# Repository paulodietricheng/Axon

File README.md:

# Axon

Axon is a single-channel mixed-signal Electromyography (EMG) acquisition and actuation system built around a custom PCB. It combines a low-noise analog front end, delta-sigma analog-to-digital conversion, and STM32 firmware for real-time signal acquisition and control of external devices.

The project emphasizes signal integrity, deterministic signal paths, and hardware/firmware co-design in a timing-constrained embedded system.

## System Architecture
Axon implements a linear signal-processing pipeline from electrodes to digital processing:

- Electrodes  
- Input Protection  
- Instrumentation Amplifier  
- Active Band-Pass Filtering  
- Delta-Sigma ADC  
- STM32 (SPI)  
- Actuation Outputs

## Analog Front End

### Input Protection
- 100 kΩ series resistor at the electrode input
- Schottky diode clamps to +5 V and −5 V
- Protects downstream circuitry from transients and overvoltage events

### Instrumentation Amplifier
- INA333 instrumentation amplifier
- Gain: 20×
- Chosen for high CMRR (~100 dB) to suppress common-mode noise inherent in EMG signals
- Reference voltage provided by a buffered ground generated using an OPA333

### Active Filtering
All active filters use OPA333 op-amps for low offset and low noise.

- High-pass Sallen–Key filter  
  - Cutoff frequency: 15 Hz  
  - Linear gain  
  - Removes DC offset and motion artifacts

- Low-pass Sallen–Key filter  
  - Cutoff frequency: 450 Hz
  - Gain: 5×
  - Limits high-frequency noise and out-of-band content

## Analog-to-Digital Conversion

- ADS131M02 delta-sigma ADC
- Differential inputs:
  - Filtered signal routed through 1 kΩ resistors to AIN0P and AIN1P
  - AIN0N and AIN1N tied to buffered ground
- ADC clock provided by an ASE 8.192 MHz oscillator
- Design considers conversion latency and group delay inherent to delta-sigma architectures

## Digital Processing & Control

### Microcontroller
- STM32 microcontroller
- Communicates with ADC via SPI
- Handles data acquisition, processing, and output control

### Programming & Debug
- JTAG / SWD interface exposed
- Signals:
  - SWDIO, SWCLK, SWO, RESET
  - RXI, TXO
  - VREF = 3.3 V

### Outputs
- Three MCU-controlled output pins routed to an external connector
- Intended for actuation or control of external devices

## Power Architecture

- USB-C power input
- Protection fuse on input
- Power rails:
  - +5 V from USB
  - −5 V generated via TPS7A inverter
  - 3.3 V generated via TPS604 DC-DC converter

## PCB Layout

- 4-layer PCB stackup:
  1. Signal
  2. Ground plane
  3. Power pours
  4. Signal
- Layout prioritizes:
  - Low-noise analog routing
  - Solid ground reference
  - Separation of analog and digital domains

## Notes

Axon serves as a completed mixed-signal system demonstrating practical considerations in low-level analog design, real-time embedded firmware, and end-to-end signal path analysis.

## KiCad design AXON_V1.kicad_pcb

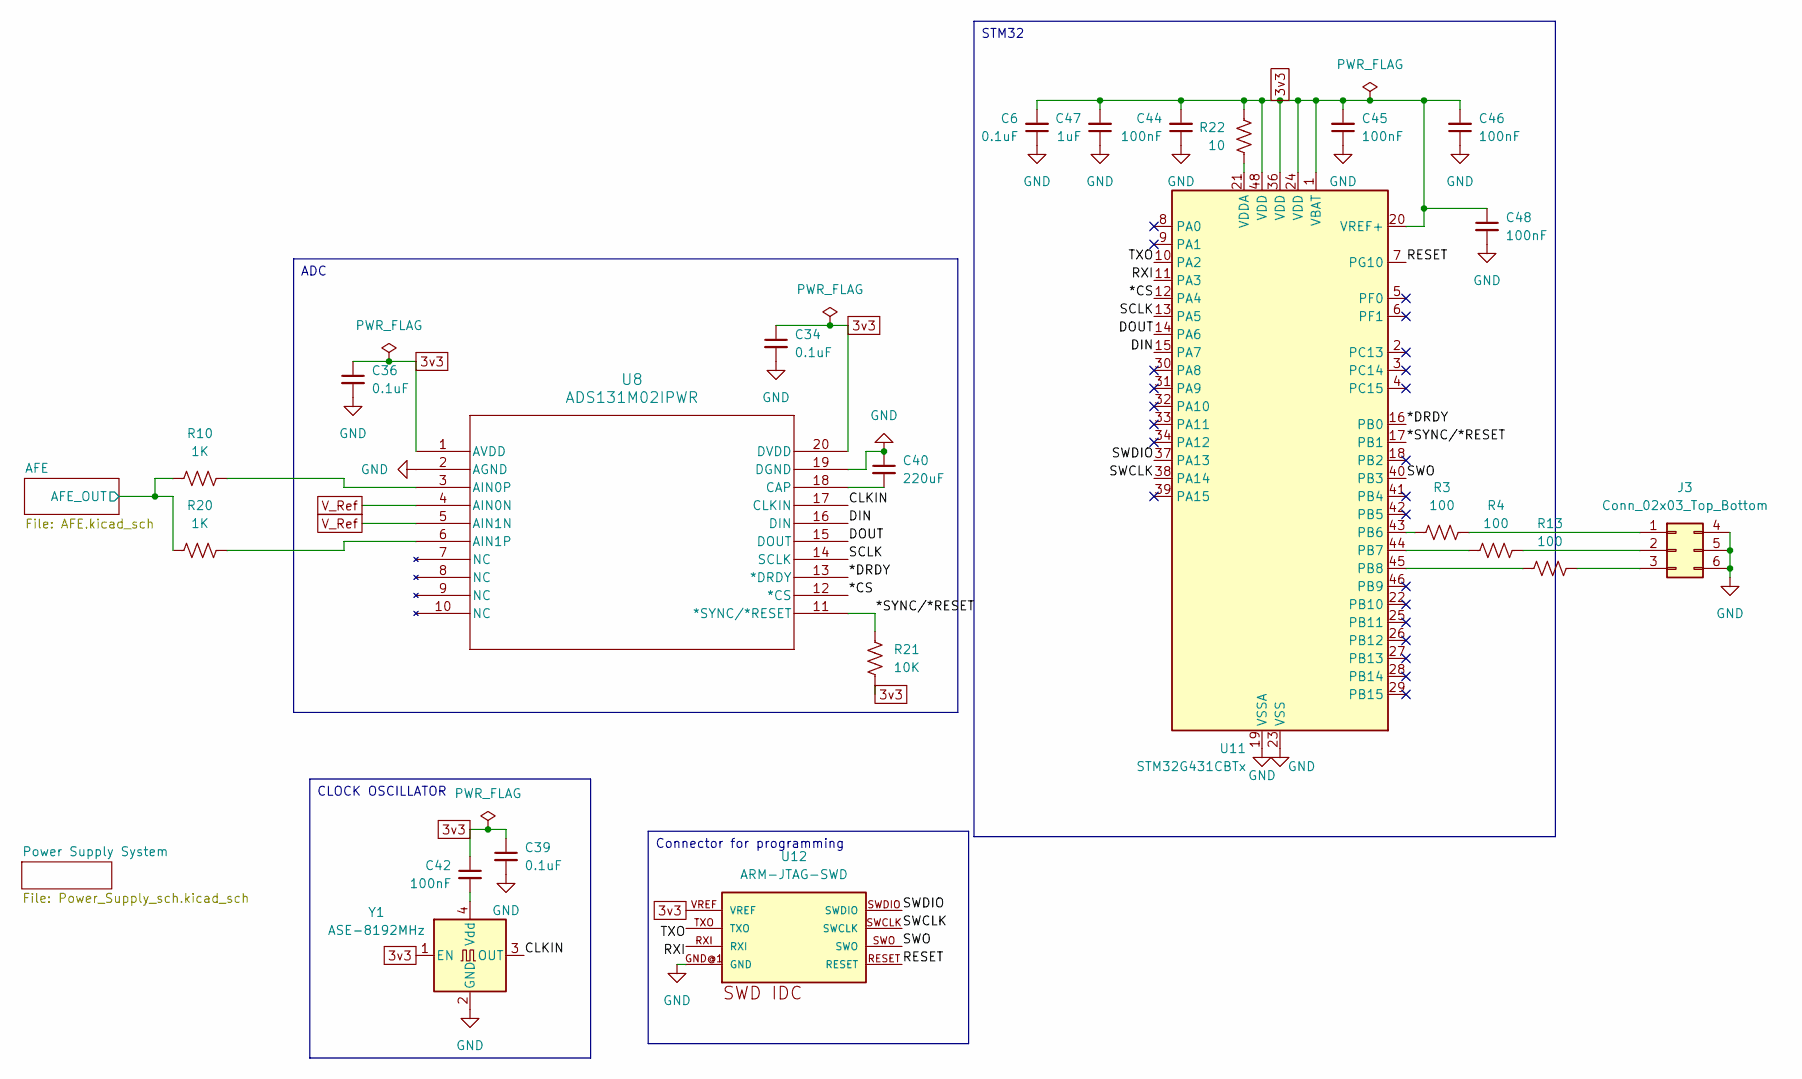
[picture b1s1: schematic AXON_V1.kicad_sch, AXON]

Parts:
C6, C34, C36, C39: 0.1uF; C_0201_0603Metric
C40: 220uF; C_0201_0603Metric
C42, C44, C45, C46, C48: 100nF; C_0201_0603Metric
C47: 1uF; C_0201_0603Metric
J3: Conn_02x03_Top_Bottom; PinSocket_2x03_P2.54mm_Vertical
R3, R4, R13: 100; R_0201_0603Metric
R10, R20: 1K; R_0201_0603Metric
R21: 10K; R_0201_0603Metric
R22: 10; R_0201_0603Metric
U8: ADS131M02IPWR; TSSOP20_PW_TEX
U11: STM32G431CBTx; LQFP-48_7x7mm_P0.5mm
U12: ARM-JTAG-SWD; ARM-JTAG-10-SWD-IDC
Y1: ASE-8192MHz; Oscillator_SMD_Abracon_ASE-4Pin_3.2x2.5mm

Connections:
3v3: C6.2, C34.1, C36.1, C39.1, C42.1, C44.2, C45.2, C46.2, C47.2, C48.1, R21.2, R22.1, U8.1 (AVDD), U8.20 (DVDD), U11.1 (VBAT), U11.20 (VREF+), U11.24 (VDD), U11.36 (VDD), U11.48 (VDD), U12.VREF, Y1.1 (EN); also elsewhere on the board
/*CS: U8.12 (*CS), U11.12 (PA4)
/*DRDY: U8.13 (*DRDY), U11.16 (PB0)
/*SYNC/*RESET: R21.1, U8.11 (*SYNC/*RESET), U11.17 (PB1)
/AFE/AFE_OUT: R10.1, R20.1; also elsewhere on the board
/CLKIN: U8.17 (CLKIN), Y1.3 (OUT)
/DIN: U8.16 (DIN), U11.15 (PA7)
/DOUT: U8.15 (DOUT), U11.14 (PA6)
/RESET: U11.7 (PG10), U12.RESET
/RXI: U11.11 (PA3), U12.RXI
/SCLK: U8.14 (SCLK), U11.13 (PA5)
/SWCLK: U11.38 (PA14), U12.SWCLK
/SWDIO: U11.37 (PA13), U12.SWDIO
/SWO: U11.40 (PB3), U12.SWO
/TXO: U11.10 (PA2), U12.TXO
GND: C6.1, C34.2, C36.2, C39.2, C40.1, C44.1, C45.1, C46.1, C47.1, C48.2, J3.4, J3.5, J3.6, U8.2 (AGND), U8.19 (DGND), U11.19 (VSSA), U11.23 (VSS), U11.35 (VSS), U11.47 (VSS), U12.GND@1 (GND), U12.GND@2 (GND), U12.GND@3 (GND), Y1.2 (GND); also elsewhere on the board
unnamed: J3.1, R3.2
unnamed: J3.2, R4.2
unnamed: J3.3, R13.2
unnamed: R10.2, U8.3 (AIN0P)
unnamed: R20.2, U8.6 (AIN1P)
unnamed: C40.2, U8.18 (CAP)
unnamed: R3.1, U11.43 (PB6)
unnamed: R4.1, U11.44 (PB7)
unnamed: R13.1, U11.45 (PB8)
unnamed: R22.2, U11.21 (VDDA)
unnamed: C42.2, Y1.4 (Vdd)
V_Ref: U8.4 (AIN0N), U8.5 (AIN1N); also elsewhere on the board

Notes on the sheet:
CLOCK OSCILLATOR
ADC
Connector for programming
STM32

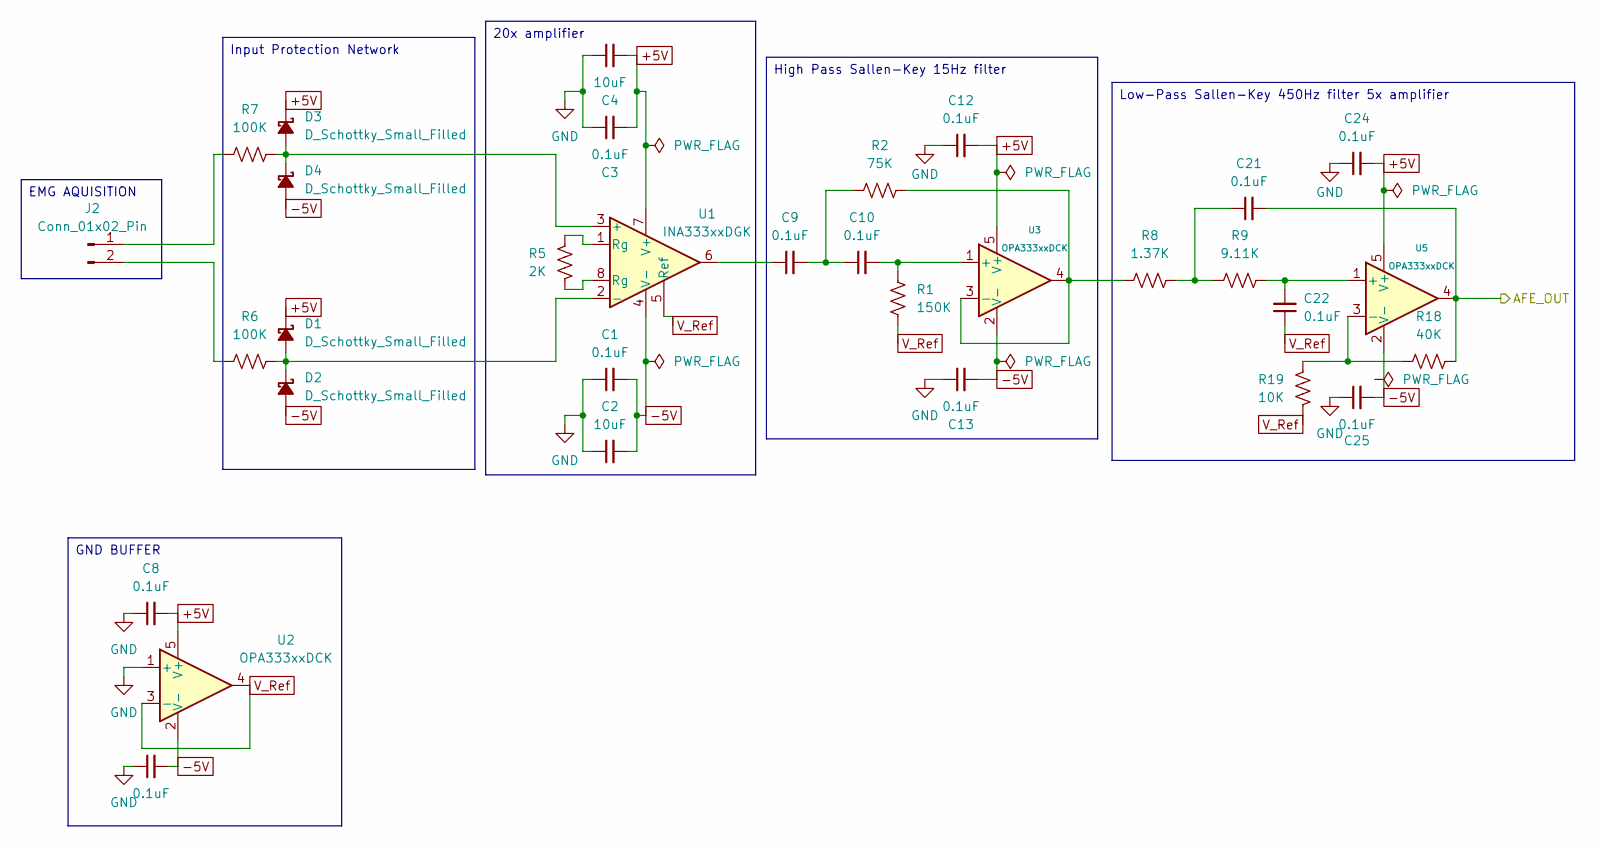
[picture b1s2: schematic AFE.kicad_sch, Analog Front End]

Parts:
C1, C3, C5, C8, C9, C10, C12, C13, C21, C22, C24, C25: 0.1uF; C_0201_0603Metric
C2, C4: 10uF; C_0201_0603Metric
D1, D2, D3, D4: D_Schottky_Small_Filled; D_0201_0603Metric
J2: Conn_01x02_Pin; JWT_A3963_1x02_P3.96mm_Vertical
R1: 150K; R_0201_0603Metric
R2: 75K; R_0201_0603Metric
R5: 2K; R_0201_0603Metric
R6, R7: 100K; R_0201_0603Metric
R8: 1.37K; R_0201_0603Metric
R9: 9.11K; R_0201_0603Metric
R18: 40K; R_0201_0603Metric
R19: 10K; R_0201_0603Metric
U1: INA333xxDGK; VSSOP-8_3x3mm_P0.65mm
U2, U3, U5: OPA333xxDCK; SOT-353_SC-70-5

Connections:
+5V: C3.2, C4.2, C8.2, C12.2, C24.2, D1.1 (K), D3.1 (K), U1.7 (V+), U2.5 (V+), U3.5 (V+), U5.5 (V+); also elsewhere on the board
-5V: C1.2, C2.2, C5.2, C13.2, C25.2, D2.2 (A), D4.2 (A), U1.4 (V-), U2.2 (V-), U3.2 (V-), U5.2 (V-); also elsewhere on the board
/AFE/AFE_OUT: C21.2, R18.2, U5.4; also elsewhere on the board
GND: C1.1, C2.1, C3.1, C4.1, C5.1, C8.1, C12.1, C13.1, C24.1, C25.1, U2.1 (+); also elsewhere on the board
unnamed: C9.1, U1.6
unnamed: C9.2, C10.1, R2.1
unnamed: C21.1, R8.2, R9.1
unnamed: D1.2 (A), D2.1 (K), R6.2, U1.2 (-)
unnamed: D3.2 (A), D4.1 (K), R7.2, U1.3 (+)
unnamed: J2.1, R7.1
unnamed: J2.2, R6.1
unnamed: R5.1, U1.1 (Rg)
unnamed: R5.2, U1.8 (Rg)
unnamed: C10.2, R1.1, U3.1 (+)
unnamed: R2.2, R8.1, U3.3 (-), U3.4
unnamed: C22.2, R9.2, U5.1 (+)
unnamed: R18.1, R19.1, U5.3 (-)
V_Ref: C22.1, R1.2, R19.2, U1.5 (Ref), U2.3 (-), U2.4; also elsewhere on the board

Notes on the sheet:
High Pass Sallen-Key 15Hz filter
GND BUFFER
Low-Pass Sallen-Key 450Hz filter 5x amplifier
Input Protection Network
20x amplifier
EMG AQUISITION

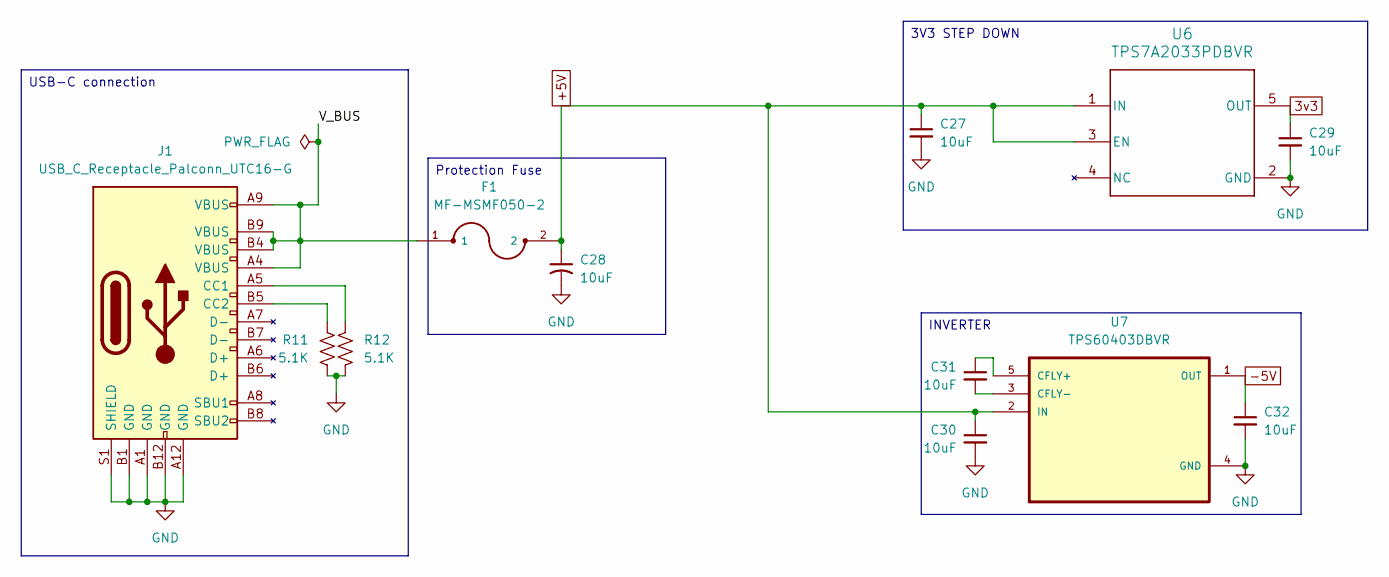
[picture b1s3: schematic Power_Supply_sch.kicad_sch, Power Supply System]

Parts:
C27, C28, C29, C30, C31, C32: 10uF; C_0201_0603Metric
F1: MF-MSMF050-2; FUSE_F050-2
J1: USB_C_Receptacle_Palconn_UTC16-G
R11, R12: 5.1K; R_0201_0603Metric
U6: TPS7A2033PDBVR; DBV0005A-IPC_A
U7: TPS60403DBVR; SOT95P280X145-5N

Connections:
3v3: C29.1, U6.5 (OUT); also elsewhere on the board
+5V: C27.1, C28.1, C30.1, F1.2, U6.1 (IN), U6.3 (EN), U7.2 (IN); also elsewhere on the board
-5V: C32.1, U7.1 (OUT); also elsewhere on the board
/Power Supply System/V_BUS: F1.1, J1.A4 (VBUS), J1.A9 (VBUS), J1.B4 (VBUS), J1.B9 (VBUS)
GND: C27.2, C28.2, C29.2, C30.2, C32.2, J1.A1 (GND), J1.A12 (GND), J1.B1 (GND), J1.B12 (GND), J1.S1 (SHIELD), R11.2, R12.2, U6.2 (GND), U7.4 (GND); also elsewhere on the board
unnamed: J1.A5 (CC1), R12.1
unnamed: J1.B5 (CC2), R11.1
unnamed: C31.1, U7.5 (CFLY+)
unnamed: C31.2, U7.3 (CFLY-)

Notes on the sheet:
USB-C connection
INVERTER
3V3 STEP DOWN
Protection Fuse

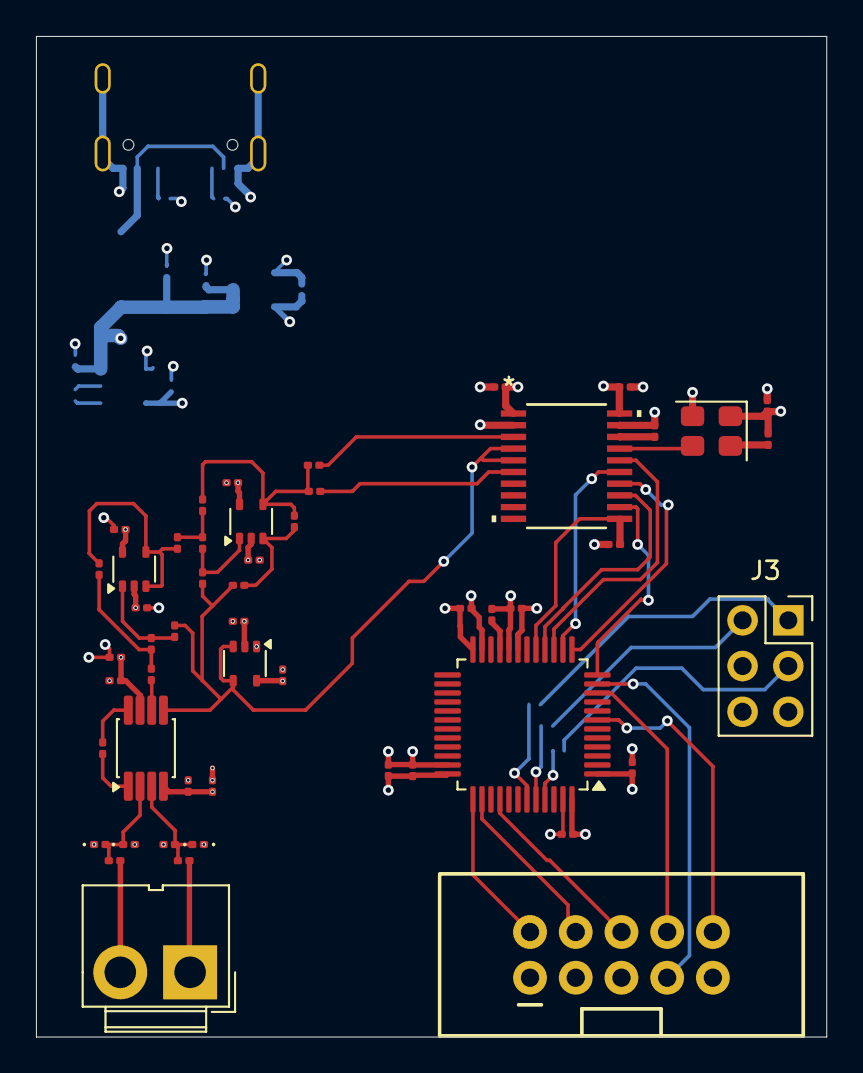
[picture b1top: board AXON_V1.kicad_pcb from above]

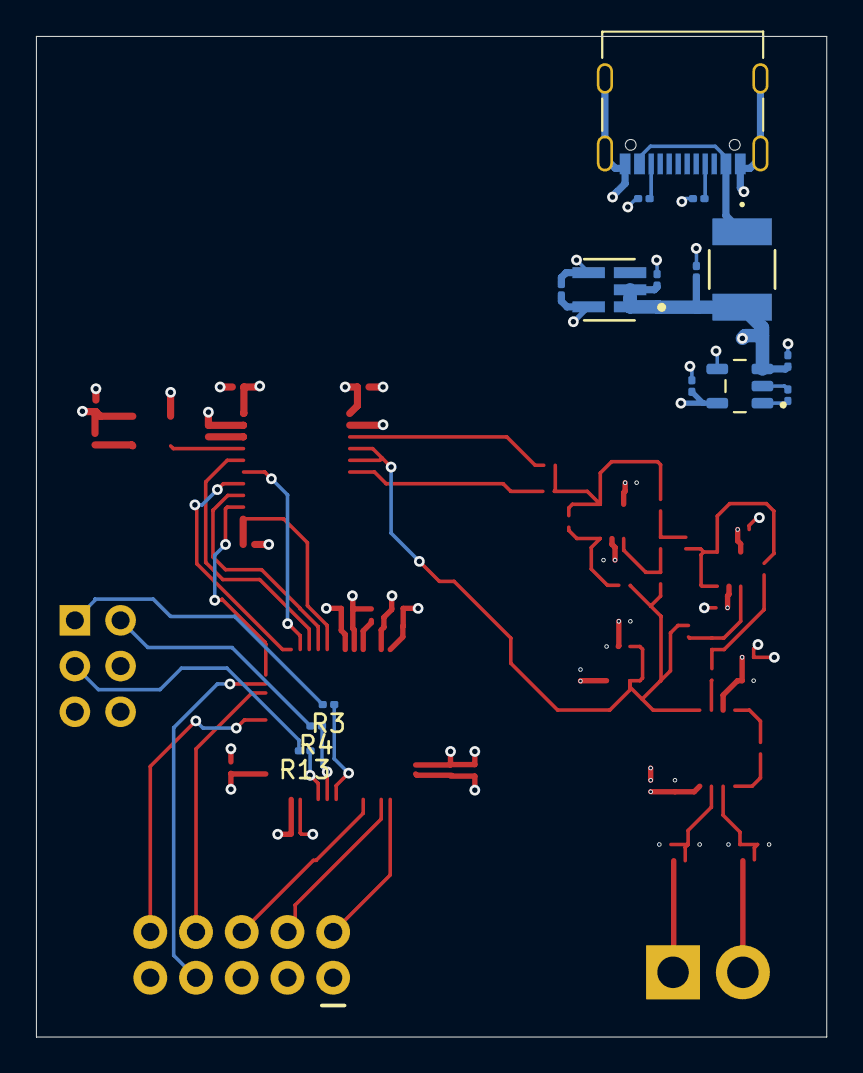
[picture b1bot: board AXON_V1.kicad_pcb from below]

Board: 4 copper layers, 43.9 x 55.6 mm, 67 parts (15 on the bottom side), 48 nets.

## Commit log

2026-01-06 Enhance README with detailed project description
    Expanded the README to provide detailed information about the Axon system architecture, analog front end, digital processing, power architecture, and PCB layout.
2026-01-06 Fix formatting of gain description in README
2026-01-12 Files added to the folder
2026-01-12 Added files via upload
2026-01-20 Fix formatting of system architecture section in README
